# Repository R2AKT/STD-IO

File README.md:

License addendum - https://github.com/R2AKT/RTC/blob/main/Addendum.txt
# STD-IO
STD IO module. For connection to the CPU_8080 processor board - https://github.com/R2AKT/CPU_8080.

Status: tested.

Модуль стандартного ввода-вывода. Для подключения к процессорной плате CPU_8080 - https://github.com/R2AKT/CPU_8080.

Статус: проверено.

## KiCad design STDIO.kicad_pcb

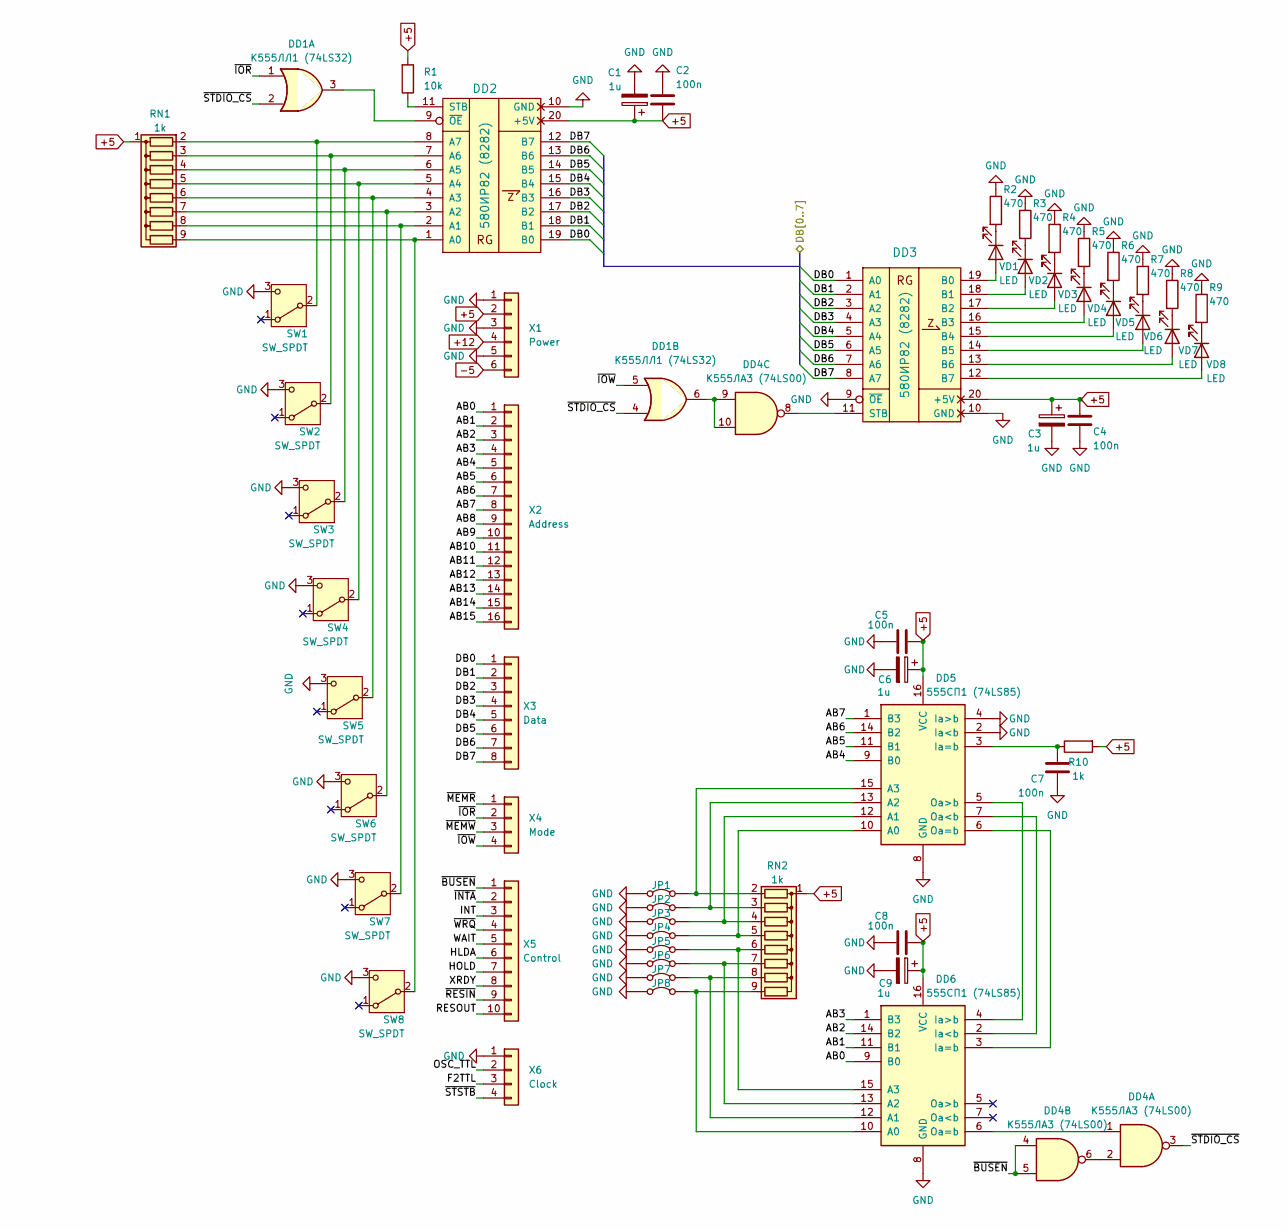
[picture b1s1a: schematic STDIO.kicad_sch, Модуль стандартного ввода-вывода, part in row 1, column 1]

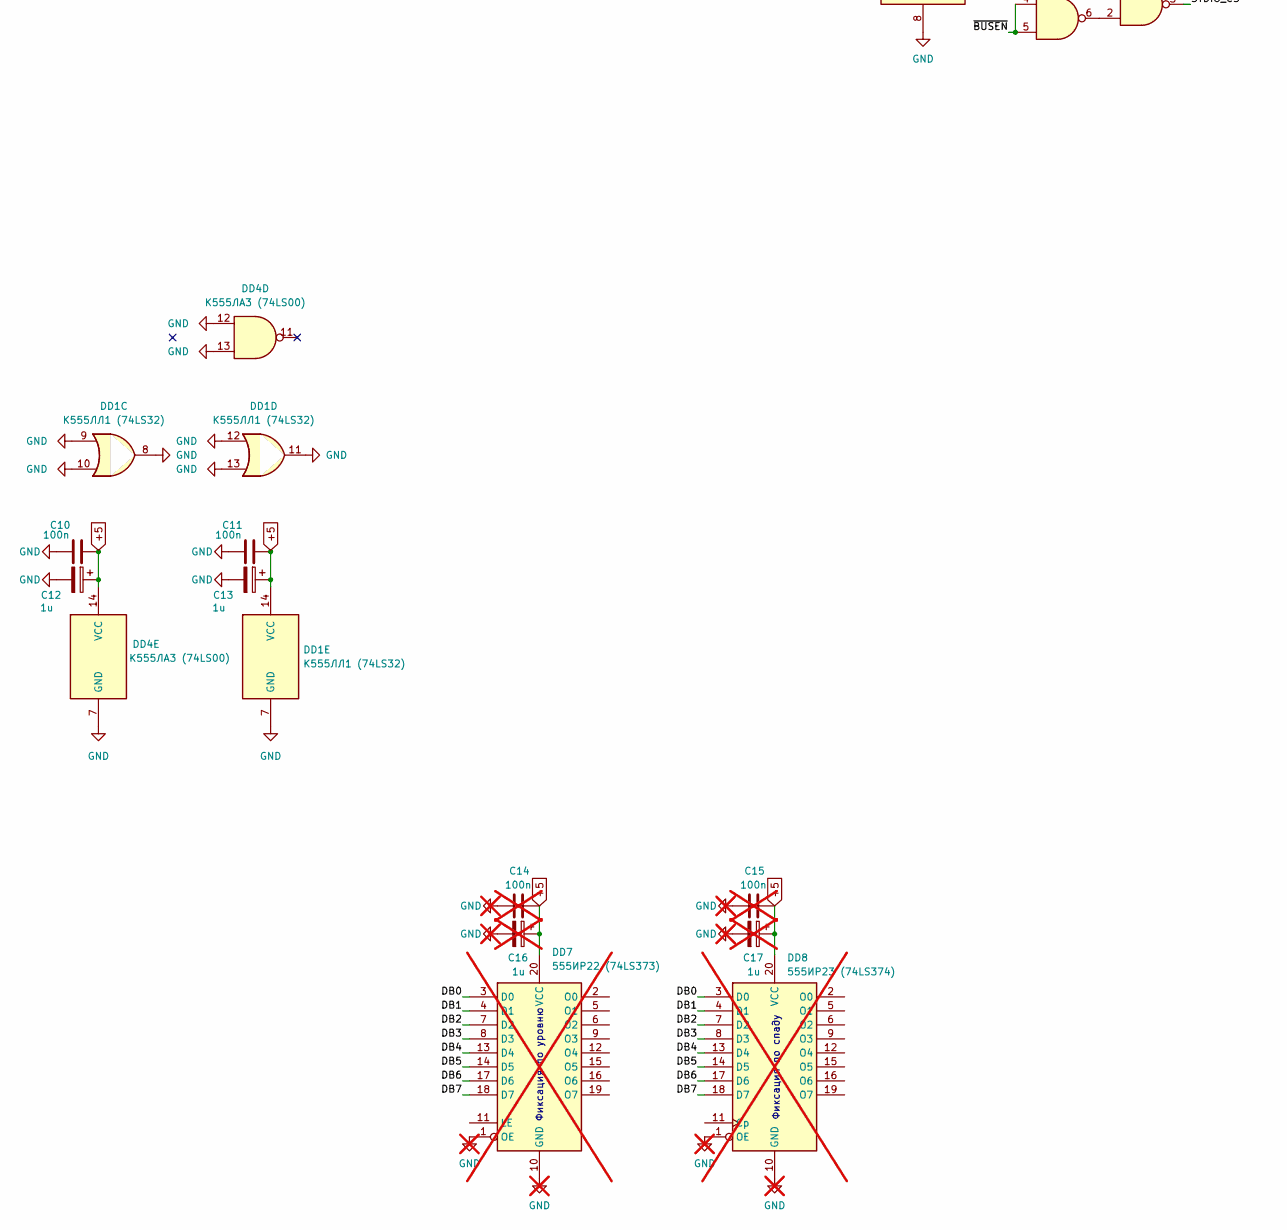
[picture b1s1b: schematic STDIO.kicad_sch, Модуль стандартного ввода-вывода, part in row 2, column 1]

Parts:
C1, C3, C6, C9, C12, C13: 1u; CP_EIA-3216-18_Kemet-A_Pad1.58x1.35mm_HandSolder
C2, C4, C5, C7, C8, C10, C11: 100n; C_0805_2012Metric_Pad1.18x1.45mm_HandSolder
C14, C15: 100n; C_0805_2012Metric_Pad1.18x1.45mm_HandSolder; not fitted
C16, C17: 1u; CP_EIA-3216-18_Kemet-A_Pad1.58x1.35mm_HandSolder; not fitted
DD1: К555ЛЛ1 (74LS32); DIP-14_W7.62mm_Socket_LongPads
DD2, DD3: 580ИР82 (8282); DIP-20_W7.62mm_Socket_LongPads
DD4: К555ЛА3 (74LS00); DIP-14_W7.62mm_Socket_LongPads
DD5, DD6: 555СП1 (74LS85); DIP-16_W7.62mm_Socket_LongPads
DD7: 555ИР22 (74LS373); not fitted
DD8: 555ИР23 (74LS374); not fitted
JP1, JP2, JP3, JP4, JP5, JP6, JP7, JP8: Jumper_2_Bridged; SolderJumper-2_P1.3mm_Bridged_RoundedPad1.0x1.5mm
R1: 10k; R_0805_2012Metric_Pad1.20x1.40mm_HandSolder
R2, R3, R4, R5, R6, R7, R8, R9: 470; R_0805_2012Metric_Pad1.20x1.40mm_HandSolder
R10: 1k; R_0805_2012Metric_Pad1.20x1.40mm_HandSolder
RN1, RN2: 1k; R_Array_SIP9
SW1, SW2, SW3, SW4, SW5, SW6, SW7, SW8: SW_SPDT; MTS-102-C4
VD1, VD2, VD3, VD4, VD5, VD6, VD7, VD8: LED; LED_0805_2012Metric_Pad1.15x1.40mm_HandSolder
X1: Power; PinHeader_1x06_P2.54mm_Vertical
X2: Address; PinHeader_1x16_P2.54mm_Vertical
X3: Data; PinHeader_1x08_P2.54mm_Vertical
X4: Mode; PinHeader_1x04_P2.54mm_Vertical
X5: Control; PinHeader_1x10_P2.54mm_Vertical
X6: Clock; PinHeader_1x04_P2.54mm_Vertical

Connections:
+5: C1.1, C2.1, C3.1, C4.1, C5.1, C6.1, C8.1, C9.1, C10.1, C11.1, C12.1, C13.1, C14.1, C15.1, C16.1, C17.1, DD1.14 (VCC), DD2.20 (+5V), DD3.20 (+5V), DD4.14 (VCC), DD5.16 (VCC), DD6.16 (VCC), DD7.20 (VCC), DD8.20 (VCC), R1.2, R10.2, RN1.1 (common), RN2.1 (common), X1.2
+12: X1.4
-5: X1.6
/AB0: DD6.9 (B0), X2.1
/AB1: DD6.11 (B1), X2.2
/AB2: DD6.14 (B2), X2.3
/AB3: DD6.1 (B3), X2.4
/AB4: DD5.9 (B0), X2.5
/AB5: DD5.11 (B1), X2.6
/AB6: DD5.14 (B2), X2.7
/AB7: DD5.1 (B3), X2.8
/AB8: X2.9
/AB9: X2.10
/AB10: X2.11
/AB11: X2.12
/AB12: X2.13
/AB13: X2.14
/AB14: X2.15
/AB15: X2.16
/DB0: DD2.19 (B0), DD3.1 (A0), DD7.3 (D0), DD8.3 (D0), X3.1
/DB1: DD2.18 (B1), DD3.2 (A1), DD7.4 (D1), DD8.4 (D1), X3.2
/DB2: DD2.17 (B2), DD3.3 (A2), DD7.7 (D2), DD8.7 (D2), X3.3
/DB3: DD2.16 (B3), DD3.4 (A3), DD7.8 (D3), DD8.8 (D3), X3.4
/DB4: DD2.15 (B4), DD3.5 (A4), DD7.13 (D4), DD8.13 (D4), X3.5
/DB5: DD2.14 (B5), DD3.6 (A5), DD7.14 (D5), DD8.14 (D5), X3.6
/DB6: DD2.13 (B6), DD3.7 (A6), DD7.17 (D6), DD8.17 (D6), X3.7
/DB7: DD2.12 (B7), DD3.8 (A7), DD7.18 (D7), DD8.18 (D7), X3.8
/F2TTL: X6.3
/HLDA: X5.6
/HOLD: X5.7
/INT: X5.3
/OSC_TTL: X6.2
/RESOUT: X5.10
/WAIT: X5.5
/XRDY: X5.8
/~BUSEN: DD4.4, DD4.5, X5.1
/~INTA: X5.2
/~IOR: DD1.1, X4.2
/~IOW: DD1.5, X4.4
/~MEMR: X4.1
/~MEMW: X4.3
/~RESIN: X5.9
/~STDIO_CS: DD1.2, DD1.4, DD4.3
/~STSTB: X6.4
/~WRQ: X5.4
GND: C1.2, C2.2, C3.2, C4.2, C5.2, C6.2, C7.2, C8.2, C9.2, C10.2, C11.2, C12.2, C13.2, C14.2, C15.2, C16.2, C17.2, DD1.7 (GND), DD1.8, DD1.9, DD1.10, DD1.11, DD1.12, DD1.13, DD2.10 (GND), DD3.9 (~OE), DD3.10 (GND), DD4.7 (GND), DD4.12, DD4.13, DD5.2 (Ia<b), DD5.4 (Ia>b), DD5.8 (GND), DD6.8 (GND), DD7.1 (OE), DD7.10 (GND), DD8.1 (OE), DD8.10 (GND), JP1.1 (A), JP2.1 (A), JP3.1 (A), JP4.1 (A), JP5.1 (A), JP6.1 (A), JP7.1 (A), JP8.1 (A), R2.1, R3.1, R4.1, R5.1, R6.1, R7.1, R8.1, R9.1, SW1.3 (C), SW2.3 (C), SW3.3 (C), SW4.3 (C), SW5.3 (C), SW6.3 (C), SW7.3 (C), SW8.3 (C), X1.1, X1.3, X1.5, X6.1
unnamed: DD1.6, DD4.9, DD4.10
unnamed: DD2.1 (A0), RN1.9 (R8), SW8.2 (B)
unnamed: DD2.2 (A1), RN1.8 (R7), SW7.2 (B)
unnamed: DD2.3 (A2), RN1.7 (R6), SW6.2 (B)
unnamed: DD2.4 (A3), RN1.6 (R5), SW5.2 (B)
unnamed: DD2.5 (A4), RN1.5 (R4), SW4.2 (B)
unnamed: DD2.6 (A5), RN1.4 (R3), SW3.2 (B)
unnamed: DD2.7 (A6), RN1.3 (R2), SW2.2 (B)
unnamed: DD2.8 (A7), RN1.2 (R1), SW1.2 (B)
unnamed: DD2.11 (STB), R1.1
unnamed: DD1.3, DD2.9 (~OE)
unnamed: DD3.19 (B0), VD1.2 (A)
unnamed: DD3.18 (B1), VD2.2 (A)
unnamed: DD3.17 (B2), VD3.2 (A)
unnamed: DD3.16 (B3), VD4.2 (A)
unnamed: DD3.15 (B4), VD5.2 (A)
unnamed: DD3.14 (B5), VD6.2 (A)
unnamed: DD3.13 (B6), VD7.2 (A)
unnamed: DD3.12 (B7), VD8.2 (A)
unnamed: DD3.11 (STB), DD4.8
unnamed: DD4.2, DD4.6
unnamed: DD5.10 (A0), JP4.2 (B), RN2.5 (R4)
unnamed: DD5.12 (A1), JP3.2 (B), RN2.4 (R3)
unnamed: DD5.13 (A2), JP2.2 (B), RN2.3 (R2)
unnamed: DD5.15 (A3), JP1.2 (B), RN2.2 (R1)
unnamed: C7.1, DD5.3 (Ia=b), R10.1
unnamed: DD5.7 (Oa<b), DD6.2 (Ia<b)
unnamed: DD5.6 (Oa=b), DD6.3 (Ia=b)
unnamed: DD5.5 (Oa>b), DD6.4 (Ia>b)
unnamed: DD6.10 (A0), JP8.2 (B), RN2.9 (R8)
unnamed: DD6.12 (A1), JP7.2 (B), RN2.8 (R7)
unnamed: DD6.13 (A2), JP6.2 (B), RN2.7 (R6)
unnamed: DD6.15 (A3), JP5.2 (B), RN2.6 (R5)
unnamed: DD4.1, DD6.6 (Oa=b)
unnamed: R2.2, VD1.1 (K)
unnamed: R3.2, VD2.1 (K)
unnamed: R4.2, VD3.1 (K)
unnamed: R5.2, VD4.1 (K)
unnamed: R6.2, VD5.1 (K)
unnamed: R7.2, VD6.1 (K)
unnamed: R8.2, VD7.1 (K)
unnamed: R9.2, VD8.1 (K)

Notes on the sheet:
Фиксация по уровню
Фиксация по спаду

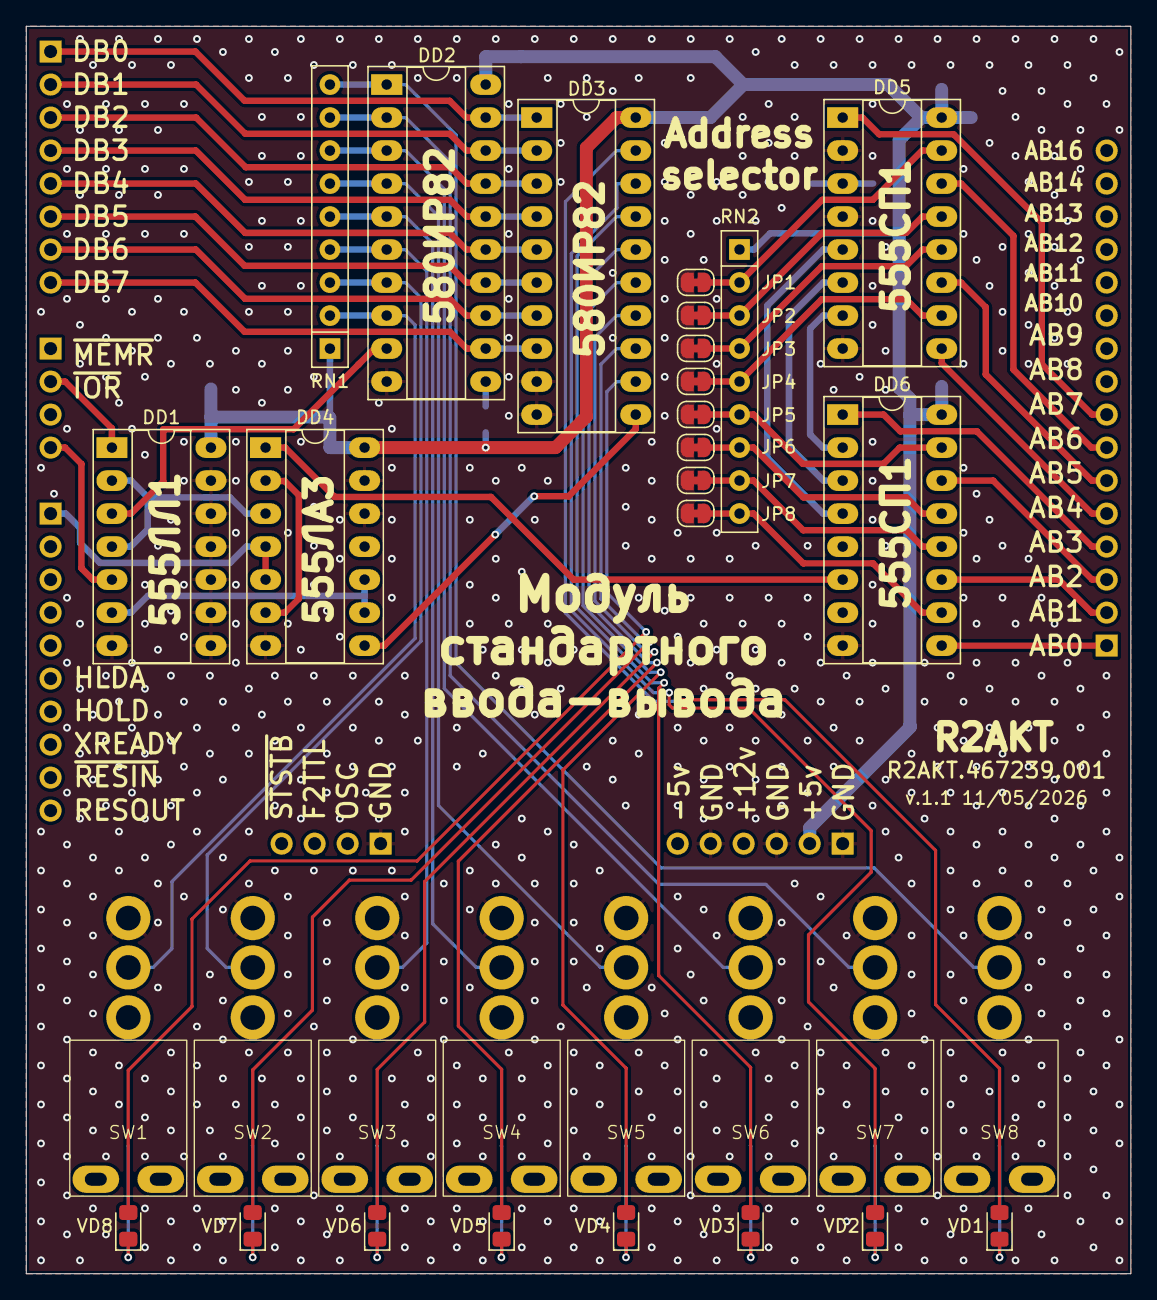
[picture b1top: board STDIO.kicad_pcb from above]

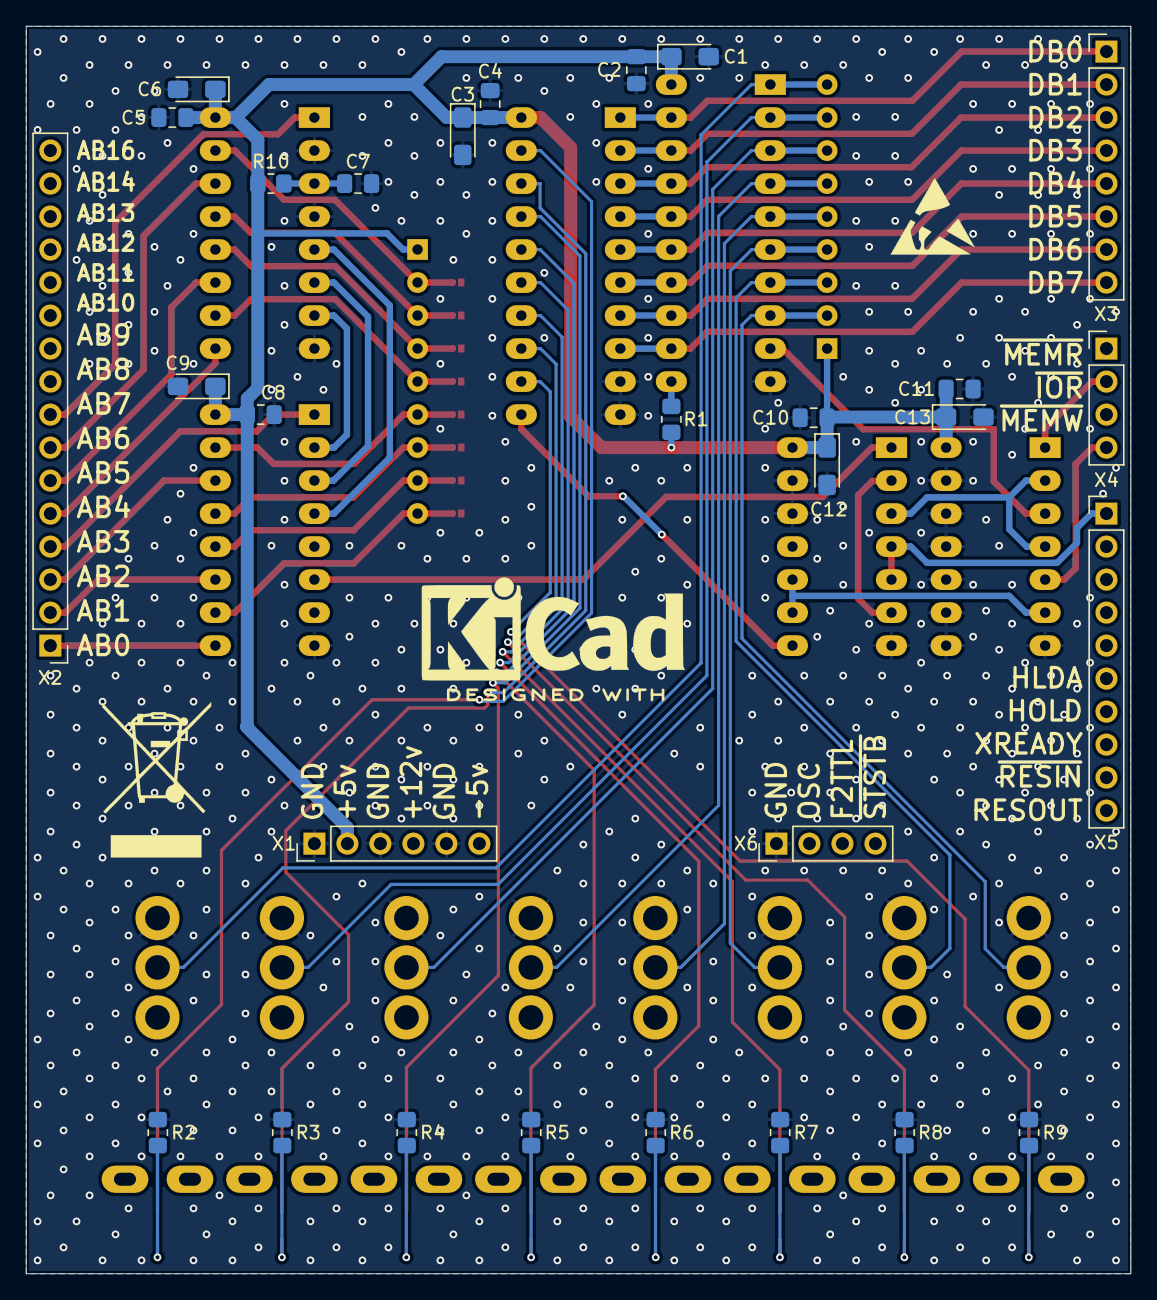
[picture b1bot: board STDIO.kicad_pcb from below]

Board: 2 copper layers, 85.0 x 96.0 mm, 61 parts (29 on the bottom side), 64 nets.

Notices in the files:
README.md:
License: MIT
